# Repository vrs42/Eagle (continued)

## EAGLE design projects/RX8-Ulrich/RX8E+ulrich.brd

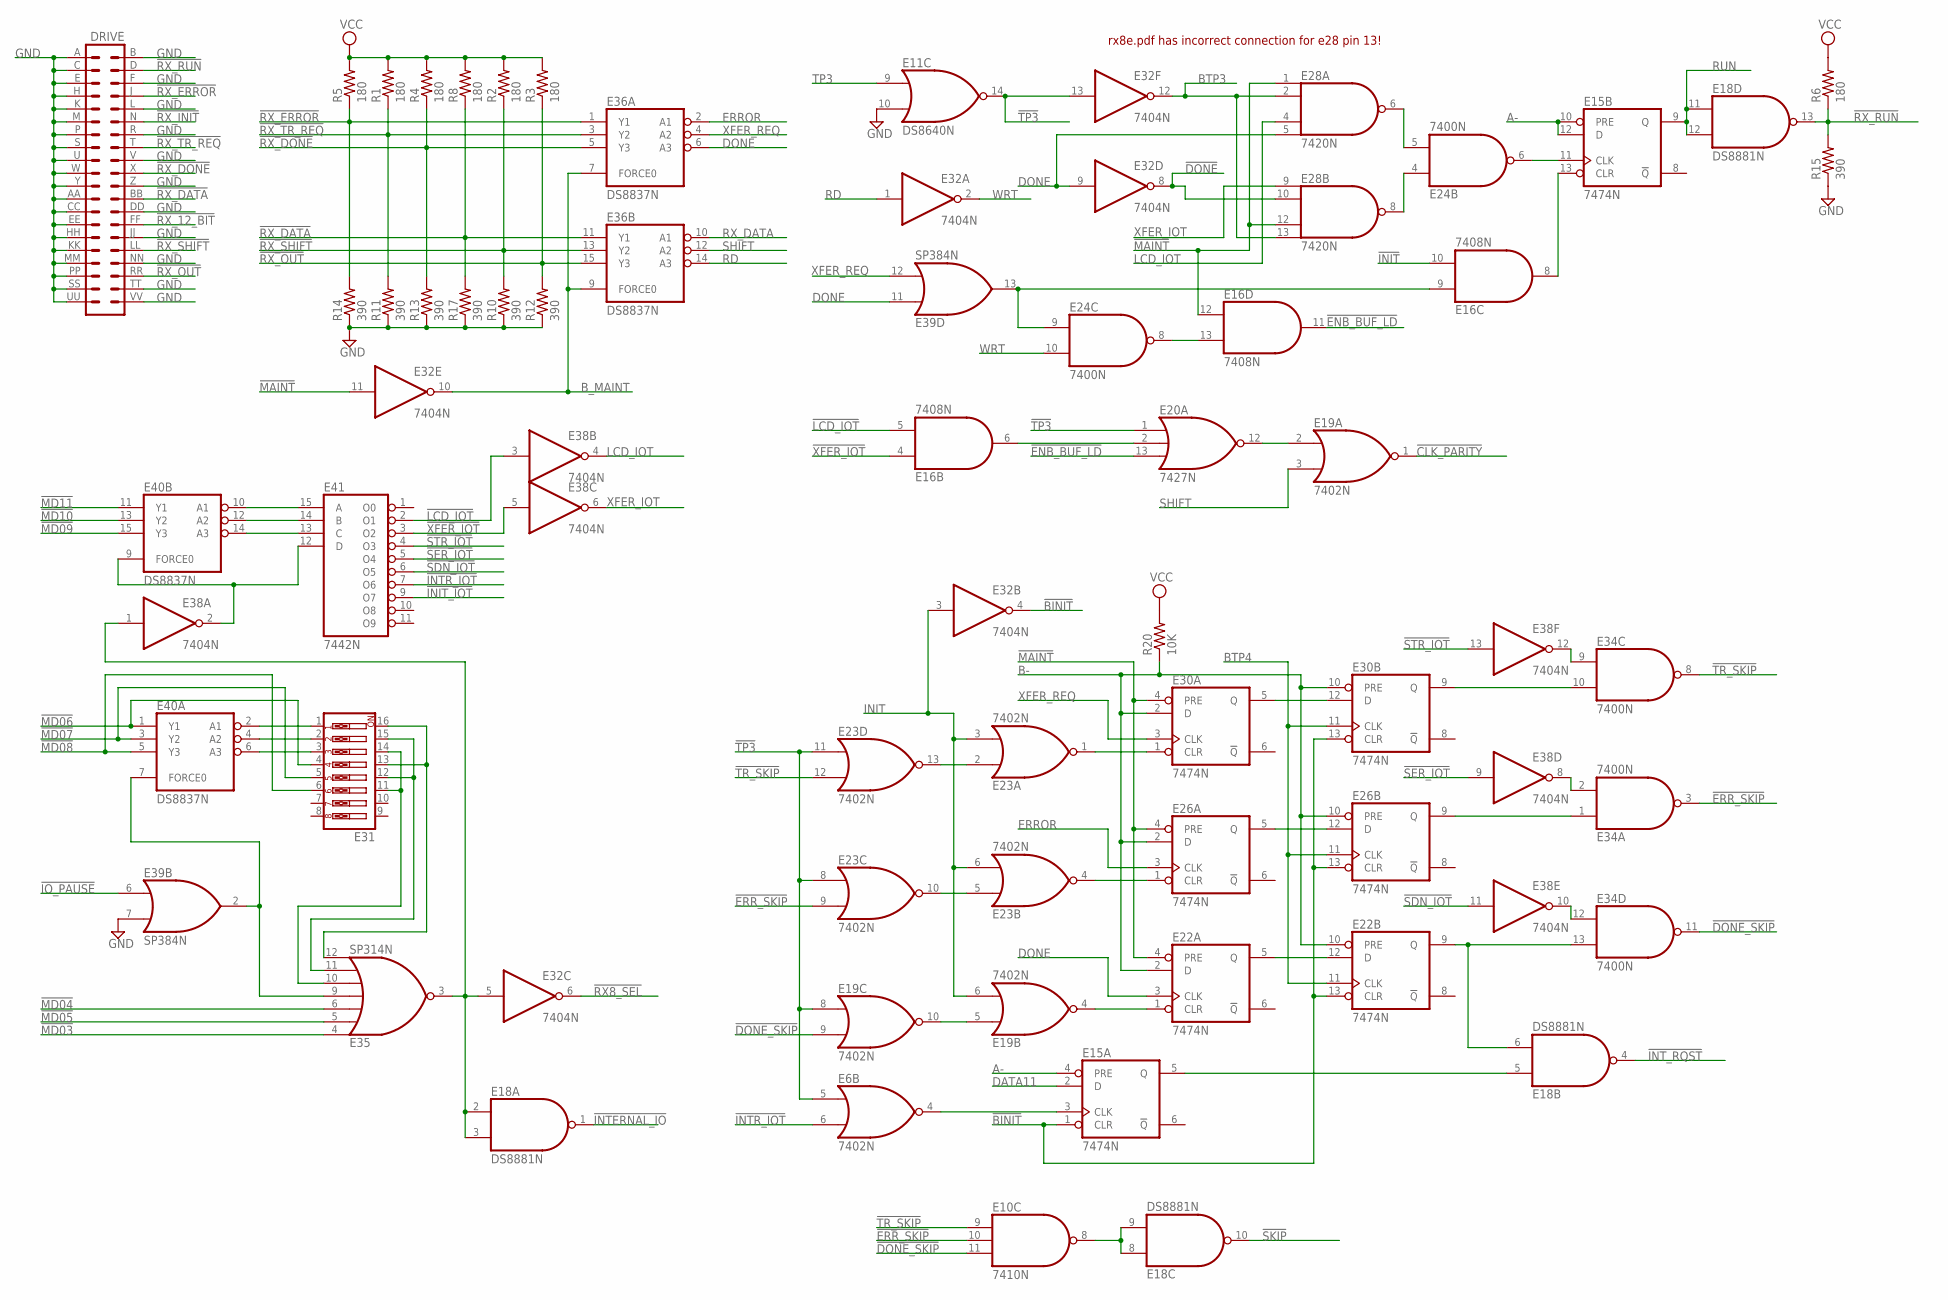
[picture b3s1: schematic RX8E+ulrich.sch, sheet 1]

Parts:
DRIVE: DEC40PINH
E6, E19, E23: 7402N; DIL14
E10: 7410N; DIL14
E11: DS8640N; DIL14
E15, E22, E26, E30: 7474N; DIL14
E16: 7408N; DIL14
E18: DS8881N; DIL14
E20: 7427N; DIL14
E24, E34: 7400N; DIL14
E28: 7420N; DIL14
E31: SW_DIP-8; EDG-08
E32, E38: 7404N; DIL14
E35: SP314N; DIL14
E36, E40: DS8837N; DIL16
E39: SP384N; DIL14
E41: 7442N; DIL16
R1, R2, R3, R4, R5, R6, R8: 180; 0207/10
R10, R11, R12, R13, R14, R15, R17: 390; 0207/10
R20: 10K; 0207/10

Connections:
!BINIT: E15.1 (CLR), E22.13 (CLR), E26.13 (CLR), E30.13 (CLR), E32.4 (O)
!CLK_PARITY: E19.1 (O); also elsewhere on the board
!DONE: E28.10 (I1), E32.8 (O); also elsewhere on the board
!DONE_SKIP: E10.11 (I2), E19.9 (I1), E34.11 (O); also elsewhere on the board
!ENB_BUF_LD: E16.11 (O), E20.13 (I2); also elsewhere on the board
!ERR_SKIP: E10.10 (I1), E23.9 (I1), E34.3 (O)
!INIT: E16.10 (I1); also elsewhere on the board
!INIT_IOT: E41.9 (O7); also elsewhere on the board
!INTERNAL_IO: E18.1 (O); also elsewhere on the board
!INTR_IOT: E6.6 (I1), E41.7 (O6)
!INT_RQST: E18.4 (O); also elsewhere on the board
!IO_PAUSE: E39.6 (I0); also elsewhere on the board
!LCD_IOT: E16.5 (I1), E38.3 (I), E41.2 (O1); also elsewhere on the board
!MAINT: E16.12 (I0), E22.4 (PRE), E26.4 (PRE), E28.1 (I0), E28.12 (I2), E30.4 (PRE), E32.11 (I); also elsewhere on the board
!MD03: E35.4 (I0); also elsewhere on the board
!MD04: E35.6 (I2); also elsewhere on the board
!MD05: E35.5 (I1); also elsewhere on the board
!MD06: E31.4, E40.1 (Y1); also elsewhere on the board
!MD07: E31.5, E40.3 (Y2); also elsewhere on the board
!MD08: E31.6, E40.5 (Y3); also elsewhere on the board
!MD09: E40.15 (Y3); also elsewhere on the board
!MD10: E40.13 (Y2); also elsewhere on the board
!MD11: E40.11 (Y1); also elsewhere on the board
!RX8_SEL: E32.6 (O); also elsewhere on the board
!RX_12_BIT: DRIVE.FF (28); also elsewhere on the board
!RX_DATA: DRIVE.BB (24), E36.11 (Y1), R8.1, R17.2; also elsewhere on the board
!RX_DONE: DRIVE.X (20), E36.5 (Y3), R4.1, R13.2
!RX_ERROR: DRIVE.J (8), E36.1 (Y1), R5.1, R14.2
!RX_INIT: DRIVE.N (12); also elsewhere on the board
!RX_OUT: DRIVE.RR (36), E36.15 (Y3), R3.1, R12.2
!RX_RUN: DRIVE.D (4), E18.13 (O), R6.1, R15.2
!RX_SHIFT: DRIVE.LL (32), E36.13 (Y2), R2.1, R10.2
!RX_TR_REQ: DRIVE.T (16), E36.3 (Y2), R1.1, R11.2
!SDN_IOT: E38.11 (I), E41.6 (O5)
!SER_IOT: E38.9 (I), E41.5 (O4)
!SKIP: E18.10 (O); also elsewhere on the board
!STR_IOT: E38.13 (I), E41.4 (O3)
!TP3: E6.5 (I0), E11.14 (O), E19.8 (I0), E20.1 (I0), E23.8 (I0), E23.11 (I0), E32.13 (I); also elsewhere on the board
!TR_SKIP: E10.9 (I0), E23.12 (I1), E34.8 (O); also elsewhere on the board
!XFER_IOT: E16.4 (I0), E38.5 (I), E41.3 (O2); also elsewhere on the board
A-: E15.4 (PRE), E15.10 (PRE), E15.12 (D); also elsewhere on the board
B-: E22.2 (D), E22.10 (PRE), E26.2 (D), E26.10 (PRE), E30.2 (D), E30.10 (PRE), R20.1; also elsewhere on the board
BTP3: E28.2 (I1), E28.13 (I3), E32.12 (O); also elsewhere on the board
BTP4: E22.11 (CLK), E26.11 (CLK), E30.11 (CLK); also elsewhere on the board
B_MAINT: E32.10 (O), E36.7 (FORCE0), E36.9 (FORCE0)
DATA11: E15.2 (D); also elsewhere on the board
DONE: E22.3 (CLK), E28.5 (I3), E32.9 (I), E36.6 (A3), E39.11 (I0); also elsewhere on the board
ERROR: E26.3 (CLK), E36.2 (A1)
GND: DRIVE.A (1), DRIVE.AA (23), DRIVE.B (2), DRIVE.C (3), DRIVE.CC (25), DRIVE.DD (26), DRIVE.E (5), DRIVE.EE (27), DRIVE.F (6), DRIVE.H (7), DRIVE.HH (29), DRIVE.JJ (30), DRIVE.K (9), DRIVE.KK (31), DRIVE.L (10), DRIVE.M (11), DRIVE.MM (33), DRIVE.NN (34), DRIVE.P (13), DRIVE.PP (35), DRIVE.R (14), DRIVE.S (15), DRIVE.SS (37), DRIVE.TT (38), DRIVE.U (17), DRIVE.UU (39), DRIVE.V (18), DRIVE.VV (40), DRIVE.W (19), DRIVE.Y (21), DRIVE.Z (22), E6.7 (GND), E10.7 (GND), E11.1 (GND), E11.10 (I1), E15.7 (GND), E16.7 (GND), E18.7 (GND), E19.7 (GND), E20.7 (GND), E22.7 (GND), E23.7 (GND), E24.7 (GND), E26.7 (GND), E28.7 (GND), E30.7 (GND), E32.7 (GND), E34.7 (GND), E35.1 (GND), E36.8 (GND), E38.7 (GND), E39.1 (GND), E39.7 (I1), E40.8 (GND), E41.8 (GND), R10.1, R11.1, R12.1, R13.1, R14.1, R15.1, R17.1; also elsewhere on the board
INIT: E19.6 (I1), E23.3 (I1), E23.6 (I1), E32.3 (I); also elsewhere on the board
LCD_IOT: E28.4 (I2), E38.4 (O); also elsewhere on the board
unnamed: E31.11, E31.14, E35.10 (I4)
unnamed: E31.12, E31.15, E35.11 (I5)
unnamed: E31.13, E31.16, E35.12 (I6)
unnamed: E31.3, E40.6 (A3)
unnamed: E31.2, E40.4 (A2)
unnamed: E31.1, E40.2 (A1)
unnamed: E35.9 (I3), E39.2 (O), E40.7 (FORCE0)
unnamed: E18.2 (I0), E18.3 (I1), E32.5 (I), E35.3 (O), E38.1 (I)
unnamed: E19.5 (I0), E19.10 (O)
unnamed: E38.2 (O), E40.9 (FORCE0), E41.12 (D)
unnamed: E40.14 (A3), E41.13 (C)
unnamed: E40.12 (A2), E41.14 (B)
unnamed: E40.10 (A1), E41.15 (A)
unnamed: E19.4 (O), E22.1 (CLR)
unnamed: E23.4 (O), E26.1 (CLR)
unnamed: E23.5 (I0), E23.10 (O)
unnamed: E23.2 (I0), E23.13 (O)
unnamed: E23.1 (O), E30.1 (CLR)
unnamed: E30.5 (Q), E30.12 (D)
unnamed: E26.5 (Q), E26.12 (D)
unnamed: E22.5 (Q), E22.12 (D)
unnamed: E18.6 (I1), E22.9 (Q), E34.13 (I1)
unnamed: E26.9 (Q), E34.1 (I0)
unnamed: E6.4 (O), E15.3 (CLK)
unnamed: E30.9 (Q), E34.10 (I1)
unnamed: E34.2 (I1), E38.8 (O)
unnamed: E34.12 (I0), E38.10 (O)
unnamed: E34.9 (I0), E38.12 (O)
unnamed: E15.5 (Q), E18.5 (I0)
unnamed: E10.8 (O), E18.8 (I0), E18.9 (I1)
unnamed: E24.5 (I1), E28.6 (O)
unnamed: E16.6 (O), E20.2 (I1)
unnamed: E24.4 (I0), E28.8 (O)
unnamed: E16.9 (I0), E24.9 (I0), E39.13 (O)
unnamed: E16.13 (I1), E24.8 (O)
unnamed: E15.13 (CLR), E16.8 (O)
unnamed: E19.2 (I0), E20.12 (O)
unnamed: E15.11 (CLK), E24.6 (O)
RD: E32.1 (I), E36.14 (A3); also elsewhere on the board
RUN: E15.9 (Q), E18.11 (I0), E18.12 (I1); also elsewhere on the board
RX_DATA: E36.10 (A1); also elsewhere on the board
SHIFT: E19.3 (I1), E36.12 (A2)
TP3: E11.9 (I0); also elsewhere on the board
VCC: E6.14 (VCC), E10.14 (VCC), E11.8 (VCC), E15.14 (VCC), E16.14 (VCC), E18.14 (VCC), E19.14 (VCC), E20.14 (VCC), E22.14 (VCC), E23.14 (VCC), E24.14 (VCC), E26.14 (VCC), E28.14 (VCC), E30.14 (VCC), E32.14 (VCC), E34.14 (VCC), E35.8 (VCC), E36.16 (VCC), E38.14 (VCC), E39.8 (VCC), E40.16 (VCC), E41.16 (VCC), R1.2, R2.2, R3.2, R4.2, R5.2, R6.2, R8.2, R20.2; also elsewhere on the board
WRT: E24.10 (I1), E32.2 (O); also elsewhere on the board
XFER_IOT: E28.9 (I0), E38.6 (O); also elsewhere on the board
XFER_REQ: E30.3 (CLK), E36.4 (A2), E39.12 (I1)

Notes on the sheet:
rx8e.pdf has incorrect connection for e28 pin 13!

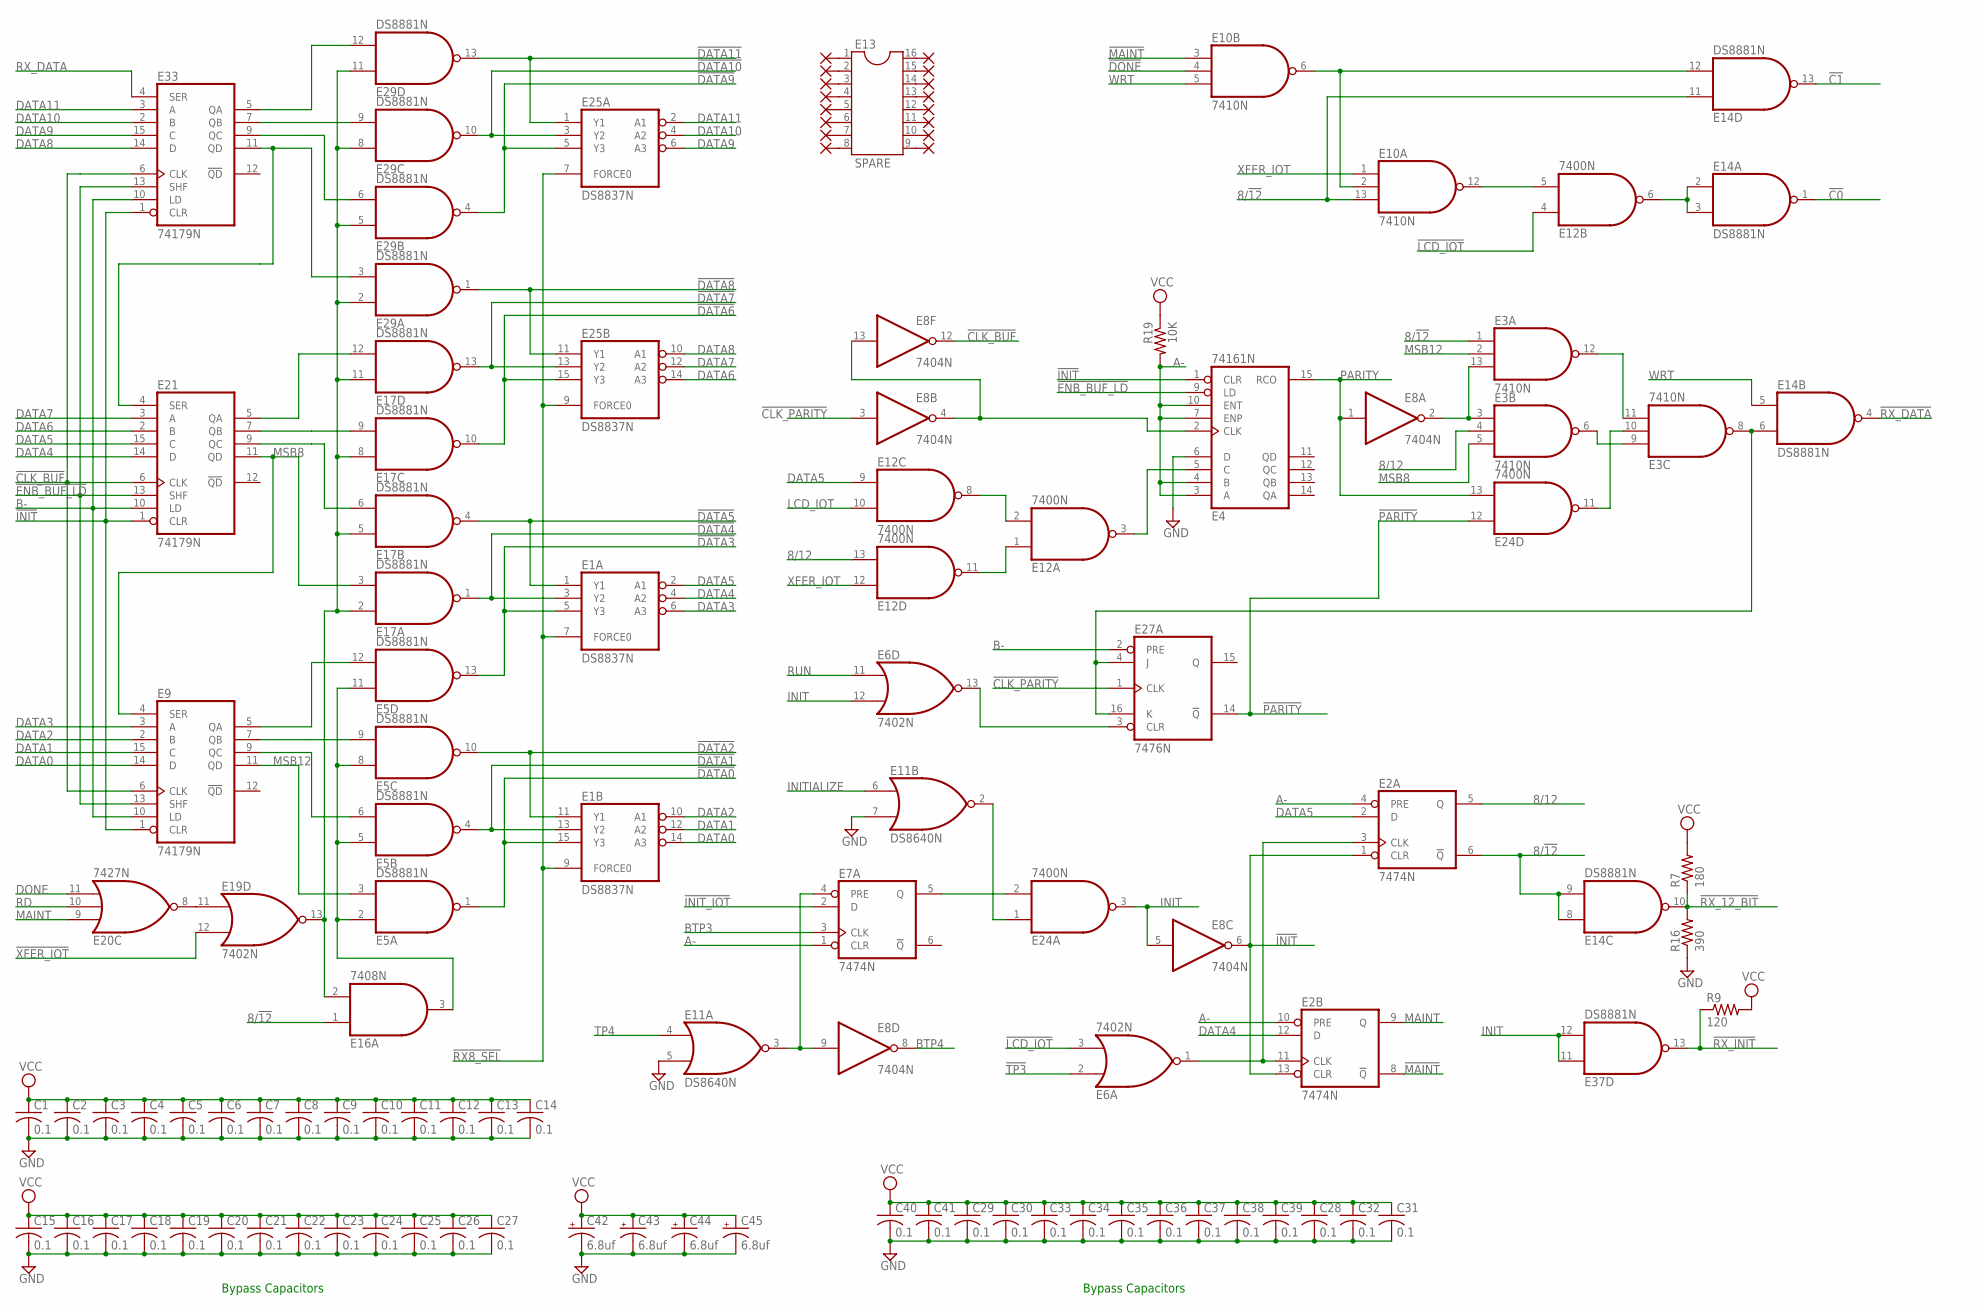
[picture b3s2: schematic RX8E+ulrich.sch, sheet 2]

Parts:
C1, C2, C3, C4, C5, C6, C7, C8, C9, C10, C11, C12, C13, C14, C15, C16, C17, C18, C19, C20, C21, C22, C23, C24, C25, C26, C27, C28, C29, C30, C31, C32, C33, C34, C35, C36, C37, C38, C39, C40, C41: 0.1; C050-025X075
C42, C43, C44, C45: 6.8uf; E22-6
E1, E25: DS8837N; DIL16
E2, E7: 7474N; DIL14
E3, E10: 7410N; DIL14
E4: 74161N; DIL16
E5, E14, E17, E29, E37: DS8881N; DIL14
E6, E19: 7402N; DIL14
E8: 7404N; DIL14
E9, E21, E33: 74179N; DIL16
E11: DS8640N; DIL14
E12, E24: 7400N; DIL14
E13: SPARE; DIL16
E16: 7408N; DIL14
E20: 7427N; DIL14
E27: 7476N; DIL16
PAD10, PAD11, PAD12, PAD13, PAD14, PAD15, PAD16, PAD17, PAD20, PAD21, PAD22, PAD23, PAD24, PAD25, PAD26, PAD27: 1,6/0,8
R7: 180; 0207/10
R9: 120; 0207/10
R16: 390; 0207/10
R19: 10K; 0207/10

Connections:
8/12: E2.5 (Q), E3.4 (I1), E12.13 (I1)
8/!12: E2.6 (!Q), E3.1 (I0), E10.13 (I2), E14.8 (I0), E14.9 (I1), E14.11 (I0), E16.1 (I0)
!C0: E14.1 (O); also elsewhere on the board
!C1: E14.13 (O); also elsewhere on the board
!CLK_BUF: E8.12 (O), E9.6 (CLK), E21.6 (CLK), E33.6 (CLK)
!CLK_PARITY: E8.3 (I), E27.1 (CLK); also elsewhere on the board
!DATA0: E1.15 (Y3), E5.1 (O); also elsewhere on the board
!DATA1: E1.13 (Y2), E5.4 (O); also elsewhere on the board
!DATA2: E1.11 (Y1), E5.10 (O); also elsewhere on the board
!DATA3: E1.5 (Y3), E5.13 (O); also elsewhere on the board
!DATA4: E1.3 (Y2), E17.1 (O); also elsewhere on the board
!DATA5: E1.1 (Y1), E17.4 (O); also elsewhere on the board
!DATA6: E17.10 (O), E25.15 (Y3); also elsewhere on the board
!DATA7: E17.13 (O), E25.13 (Y2); also elsewhere on the board
!DATA8: E25.11 (Y1), E29.1 (O); also elsewhere on the board
!DATA9: E25.5 (Y3), E29.4 (O); also elsewhere on the board
!DATA10: E25.3 (Y2), E29.10 (O); also elsewhere on the board
!DATA11: E25.1 (Y1), E29.13 (O); also elsewhere on the board
!DONE: E10.4 (I1); also elsewhere on the board
!ENB_BUF_LD: E4.9 (LD), E9.13 (SHF), E21.13 (SHF), E33.13 (SHF); also elsewhere on the board
!INIT: E2.1 (CLR), E2.13 (CLR), E4.1 (CLR), E8.6 (O), E9.1 (CLR), E21.1 (CLR), E33.1 (CLR); also elsewhere on the board
!INIT_IOT: E7.2 (D); also elsewhere on the board
!LCD_IOT: E6.3 (I1), E12.4 (I0); also elsewhere on the board
!MAINT: E2.8 (!Q), E10.3 (I0); also elsewhere on the board
!PARITY: E24.12 (I0), E27.14 (!Q)
!RX8_SEL: E1.7 (FORCE0), E1.9 (FORCE0), E25.7 (FORCE0), E25.9 (FORCE0); also elsewhere on the board
!RX_12_BIT: E14.10 (O), R7.1, R16.2; also elsewhere on the board
!RX_DATA: E14.4 (O); also elsewhere on the board
!RX_INIT: E37.13 (O), R9.1; also elsewhere on the board
!TP3: E6.2 (I0); also elsewhere on the board
!XFER_IOT: E19.12 (I1); also elsewhere on the board
A-: E2.4 (PRE), E2.10 (PRE), E4.3 (A), E4.4 (B), E4.7 (ENP), E4.10 (ENT), E7.1 (CLR), R19.2; also elsewhere on the board
B-: E9.10 (LD), E21.10 (LD), E27.2 (PRE), E33.10 (LD); also elsewhere on the board
BTP3: E7.3 (CLK); also elsewhere on the board
BTP4: E8.8 (O); also elsewhere on the board
DATA0: E1.14 (A3), E9.14 (D)
DATA1: E1.12 (A2), E9.15 (C)
DATA2: E1.10 (A1), E9.2 (B)
DATA3: E1.6 (A3), E9.3 (A)
DATA4: E1.4 (A2), E2.12 (D), E21.14 (D)
DATA5: E1.2 (A1), E2.2 (D), E12.9 (I0), E21.15 (C)
DATA6: E21.2 (B), E25.14 (A3)
DATA7: E21.3 (A), E25.12 (A2)
DATA8: E25.10 (A1), E33.14 (D)
DATA9: E25.6 (A3), E33.15 (C)
DATA10: E25.4 (A2), E33.2 (B)
DATA11: E25.2 (A1), E33.3 (A); also elsewhere on the board
DONE: E20.11 (I2); also elsewhere on the board
GND: C1.2, C2.2, C3.2, C4.2, C5.2, C6.2, C7.2, C8.2, C9.2, C10.2, C11.2, C12.2, C13.2, C14.2, C15.2, C16.2, C17.2, C18.2, C19.2, C20.2, C21.2, C22.2, C23.2, C24.2, C25.2, C26.2, C27.2, C28.2, C29.2, C30.2, C31.2, C32.2, C33.2, C34.2, C35.2, C36.2, C37.2, C38.2, C39.2, C40.2, C41.2, C42.-, C43.-, C44.-, C45.-, E1.8 (GND), E2.7 (GND), E3.7 (GND), E4.6 (D), E4.8 (GND), E5.7 (GND), E6.7 (GND), E7.7 (GND), E8.7 (GND), E9.8 (GND), E10.7 (GND), E11.1 (GND), E11.5 (I1), E11.7 (I1), E12.7 (GND), E14.7 (GND), E16.7 (GND), E17.7 (GND), E19.7 (GND), E20.7 (GND), E21.8 (GND), E24.7 (GND), E25.8 (GND), E27.13 (GND), E29.7 (GND), E33.8 (GND), E37.7 (GND), R16.1; also elsewhere on the board
INIT: E6.12 (I1), E8.5 (I), E24.3 (O), E37.11 (I0), E37.12 (I1); also elsewhere on the board
INITIALIZE: E11.6 (I0); also elsewhere on the board
LCD_IOT: E12.10 (I1); also elsewhere on the board
MAINT: E2.9 (Q), E20.9 (I0)
MSB8: E3.5 (I2), E9.4 (SER), E17.3 (I1), E21.11 (QD)
MSB12: E3.2 (I1), E5.3 (I1), E9.11 (QD)
unnamed: E5.9 (I1), E9.7 (QB)
unnamed: E16.2 (I1), E17.2 (I0), E17.5 (I0), E17.8 (I0), E17.11 (I0), E19.13 (O), E29.2 (I0), E29.5 (I0), E29.8 (I0), E29.11 (I0)
unnamed: E19.11 (I0), E20.8 (O)
unnamed: E5.2 (I0), E5.5 (I0), E5.8 (I0), E5.11 (I0), E16.3 (O)
unnamed: E13.1, PAD10.1
unnamed: E13.2, PAD11.1
unnamed: E13.3, PAD12.1
unnamed: E13.4, PAD13.1
unnamed: E13.5, PAD14.1
unnamed: E13.6, PAD15.1
unnamed: E13.7, PAD16.1
unnamed: E13.8, PAD17.1
unnamed: E4.5 (C), E12.3 (O)
unnamed: E12.6 (O), E14.2 (I0), E14.3 (I1)
unnamed: E13.16, PAD20.1
unnamed: E13.15, PAD21.1
unnamed: E13.14, PAD22.1
unnamed: E13.13, PAD23.1
unnamed: E13.12, PAD24.1
unnamed: E13.11, PAD25.1
unnamed: E13.10, PAD26.1
unnamed: E13.9, PAD27.1
unnamed: E21.4 (SER), E29.3 (I1), E33.11 (QD)
unnamed: E10.12 (O), E12.5 (I1)
unnamed: E5.6 (I1), E9.9 (QC)
unnamed: E10.2 (I1), E10.6 (O), E14.12 (I1)
unnamed: E12.1 (I0), E12.11 (O)
unnamed: E12.2 (I1), E12.8 (O)
unnamed: E3.3 (I0), E3.13 (I2), E8.2 (O)
unnamed: E3.11 (I2), E3.12 (O)
unnamed: E3.6 (O), E3.9 (I0)
unnamed: E3.10 (I1), E24.11 (O)
unnamed: E3.8 (O), E14.6 (I1), E27.4 (J), E27.16 (K)
unnamed: E7.4 (PRE), E8.9 (I), E11.3 (O)
unnamed: E4.2 (CLK), E8.4 (O), E8.13 (I)
unnamed: E7.5 (Q), E24.2 (I1)
unnamed: E6.13 (O), E27.3 (CLR)
unnamed: E11.2 (O), E24.1 (I0)
unnamed: E2.3 (CLK), E2.11 (CLK), E6.1 (O)
unnamed: E5.12 (I1), E9.5 (QA)
unnamed: E17.6 (I1), E21.9 (QC)
unnamed: E17.9 (I1), E21.7 (QB)
unnamed: E17.12 (I1), E21.5 (QA)
unnamed: E29.12 (I1), E33.5 (QA)
unnamed: E29.6 (I1), E33.9 (QC)
unnamed: E29.9 (I1), E33.7 (QB)
PARITY: E4.15 (RCO), E8.1 (I), E24.13 (I1); also elsewhere on the board
RD: E20.10 (I1); also elsewhere on the board
RUN: E6.11 (I0); also elsewhere on the board
RX_DATA: E33.4 (SER); also elsewhere on the board
TP4: E11.4 (I0); also elsewhere on the board
VCC: C1.1, C2.1, C3.1, C4.1, C5.1, C6.1, C7.1, C8.1, C9.1, C10.1, C11.1, C12.1, C13.1, C14.1, C15.1, C16.1, C17.1, C18.1, C19.1, C20.1, C21.1, C22.1, C23.1, C24.1, C25.1, C26.1, C27.1, C28.1, C29.1, C30.1, C31.1, C32.1, C33.1, C34.1, C35.1, C36.1, C37.1, C38.1, C39.1, C40.1, C41.1, C42.+, C43.+, C44.+, C45.+, E1.16 (VCC), E2.14 (VCC), E3.14 (VCC), E4.16 (VCC), E5.14 (VCC), E6.14 (VCC), E7.14 (VCC), E8.14 (VCC), E9.16 (VCC), E10.14 (VCC), E11.8 (VCC), E12.14 (VCC), E14.14 (VCC), E16.14 (VCC), E17.14 (VCC), E19.14 (VCC), E20.14 (VCC), E21.16 (VCC), E24.14 (VCC), E25.16 (VCC), E27.5 (VCC), E29.14 (VCC), E33.16 (VCC), E37.14 (VCC), R7.2, R9.2, R19.1; also elsewhere on the board
WRT: E10.5 (I2), E14.5 (I0); also elsewhere on the board
XFER_IOT: E10.1 (I0), E12.12 (I0); also elsewhere on the board

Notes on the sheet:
Bypass Capacitors

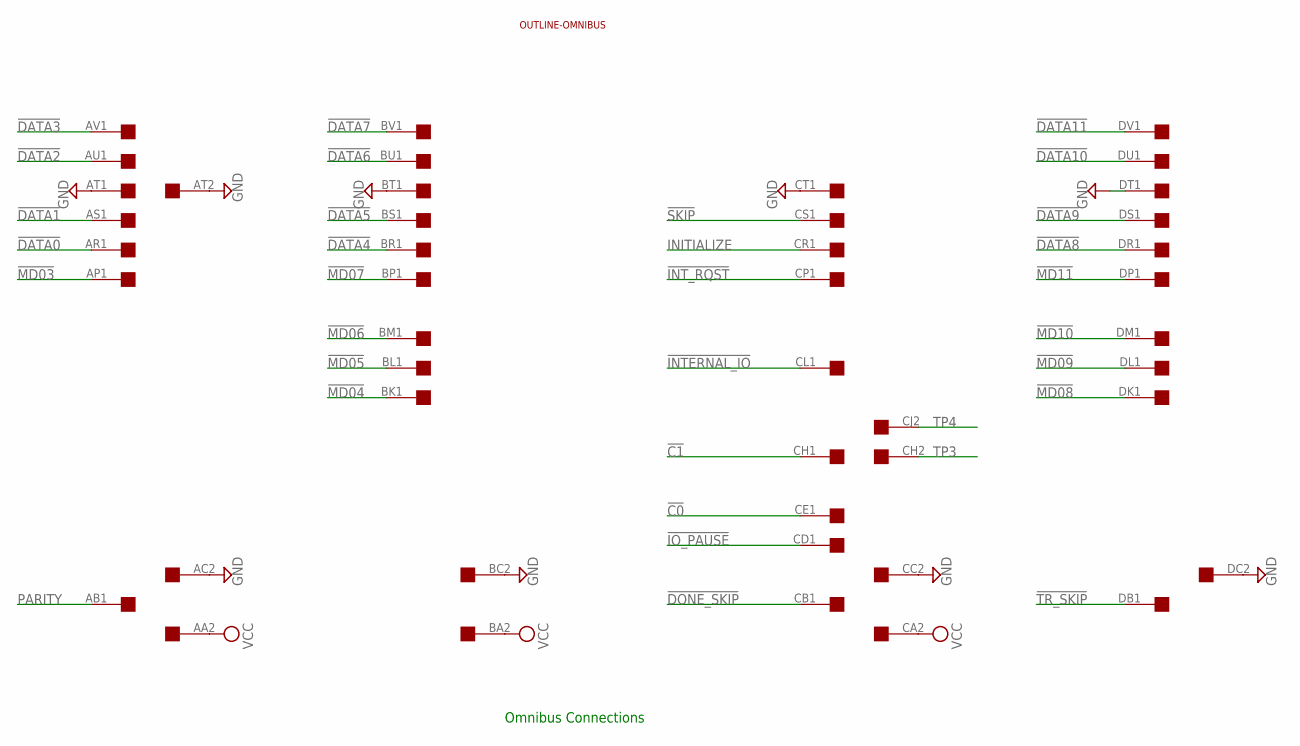
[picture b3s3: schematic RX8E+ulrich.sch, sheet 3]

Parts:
U$2: QUAD; EDGE-CON8
U$5: OUTLINE-OMNIBUS; OMNIBUS

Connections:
!C0: U$2.CE1; also elsewhere on the board
!C1: U$2.CH1; also elsewhere on the board
!DATA0: U$2.AR1; also elsewhere on the board
!DATA1: U$2.AS1; also elsewhere on the board
!DATA2: U$2.AU1; also elsewhere on the board
!DATA3: U$2.AV1; also elsewhere on the board
!DATA4: U$2.BR1; also elsewhere on the board
!DATA5: U$2.BS1; also elsewhere on the board
!DATA6: U$2.BU1; also elsewhere on the board
!DATA7: U$2.BV1; also elsewhere on the board
!DATA8: U$2.DR1; also elsewhere on the board
!DATA9: U$2.DS1; also elsewhere on the board
!DATA10: U$2.DU1; also elsewhere on the board
!DATA11: U$2.DV1; also elsewhere on the board
!DONE_SKIP: U$2.CB1; also elsewhere on the board
!INTERNAL_IO: U$2.CL1; also elsewhere on the board
!INT_RQST: U$2.CP1; also elsewhere on the board
!IO_PAUSE: U$2.CD1; also elsewhere on the board
!MD03: U$2.AP1; also elsewhere on the board
!MD04: U$2.BK1; also elsewhere on the board
!MD05: U$2.BL1; also elsewhere on the board
!MD06: U$2.BM1; also elsewhere on the board
!MD07: U$2.BP1; also elsewhere on the board
!MD08: U$2.DK1; also elsewhere on the board
!MD09: U$2.DL1; also elsewhere on the board
!MD10: U$2.DM1; also elsewhere on the board
!MD11: U$2.DP1; also elsewhere on the board
!SKIP: U$2.CS1; also elsewhere on the board
!TR_SKIP: U$2.DB1; also elsewhere on the board
GND: U$2.AC2, U$2.AT1, U$2.AT2, U$2.BC2, U$2.BT1, U$2.CC2, U$2.CT1, U$2.DC2, U$2.DT1; also elsewhere on the board
INITIALIZE: U$2.CR1; also elsewhere on the board
PARITY: U$2.AB1; also elsewhere on the board
TP3: U$2.CH2; also elsewhere on the board
TP4: U$2.CJ2; also elsewhere on the board
VCC: U$2.AA2, U$2.BA2, U$2.CA2; also elsewhere on the board

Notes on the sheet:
Omnibus Connections

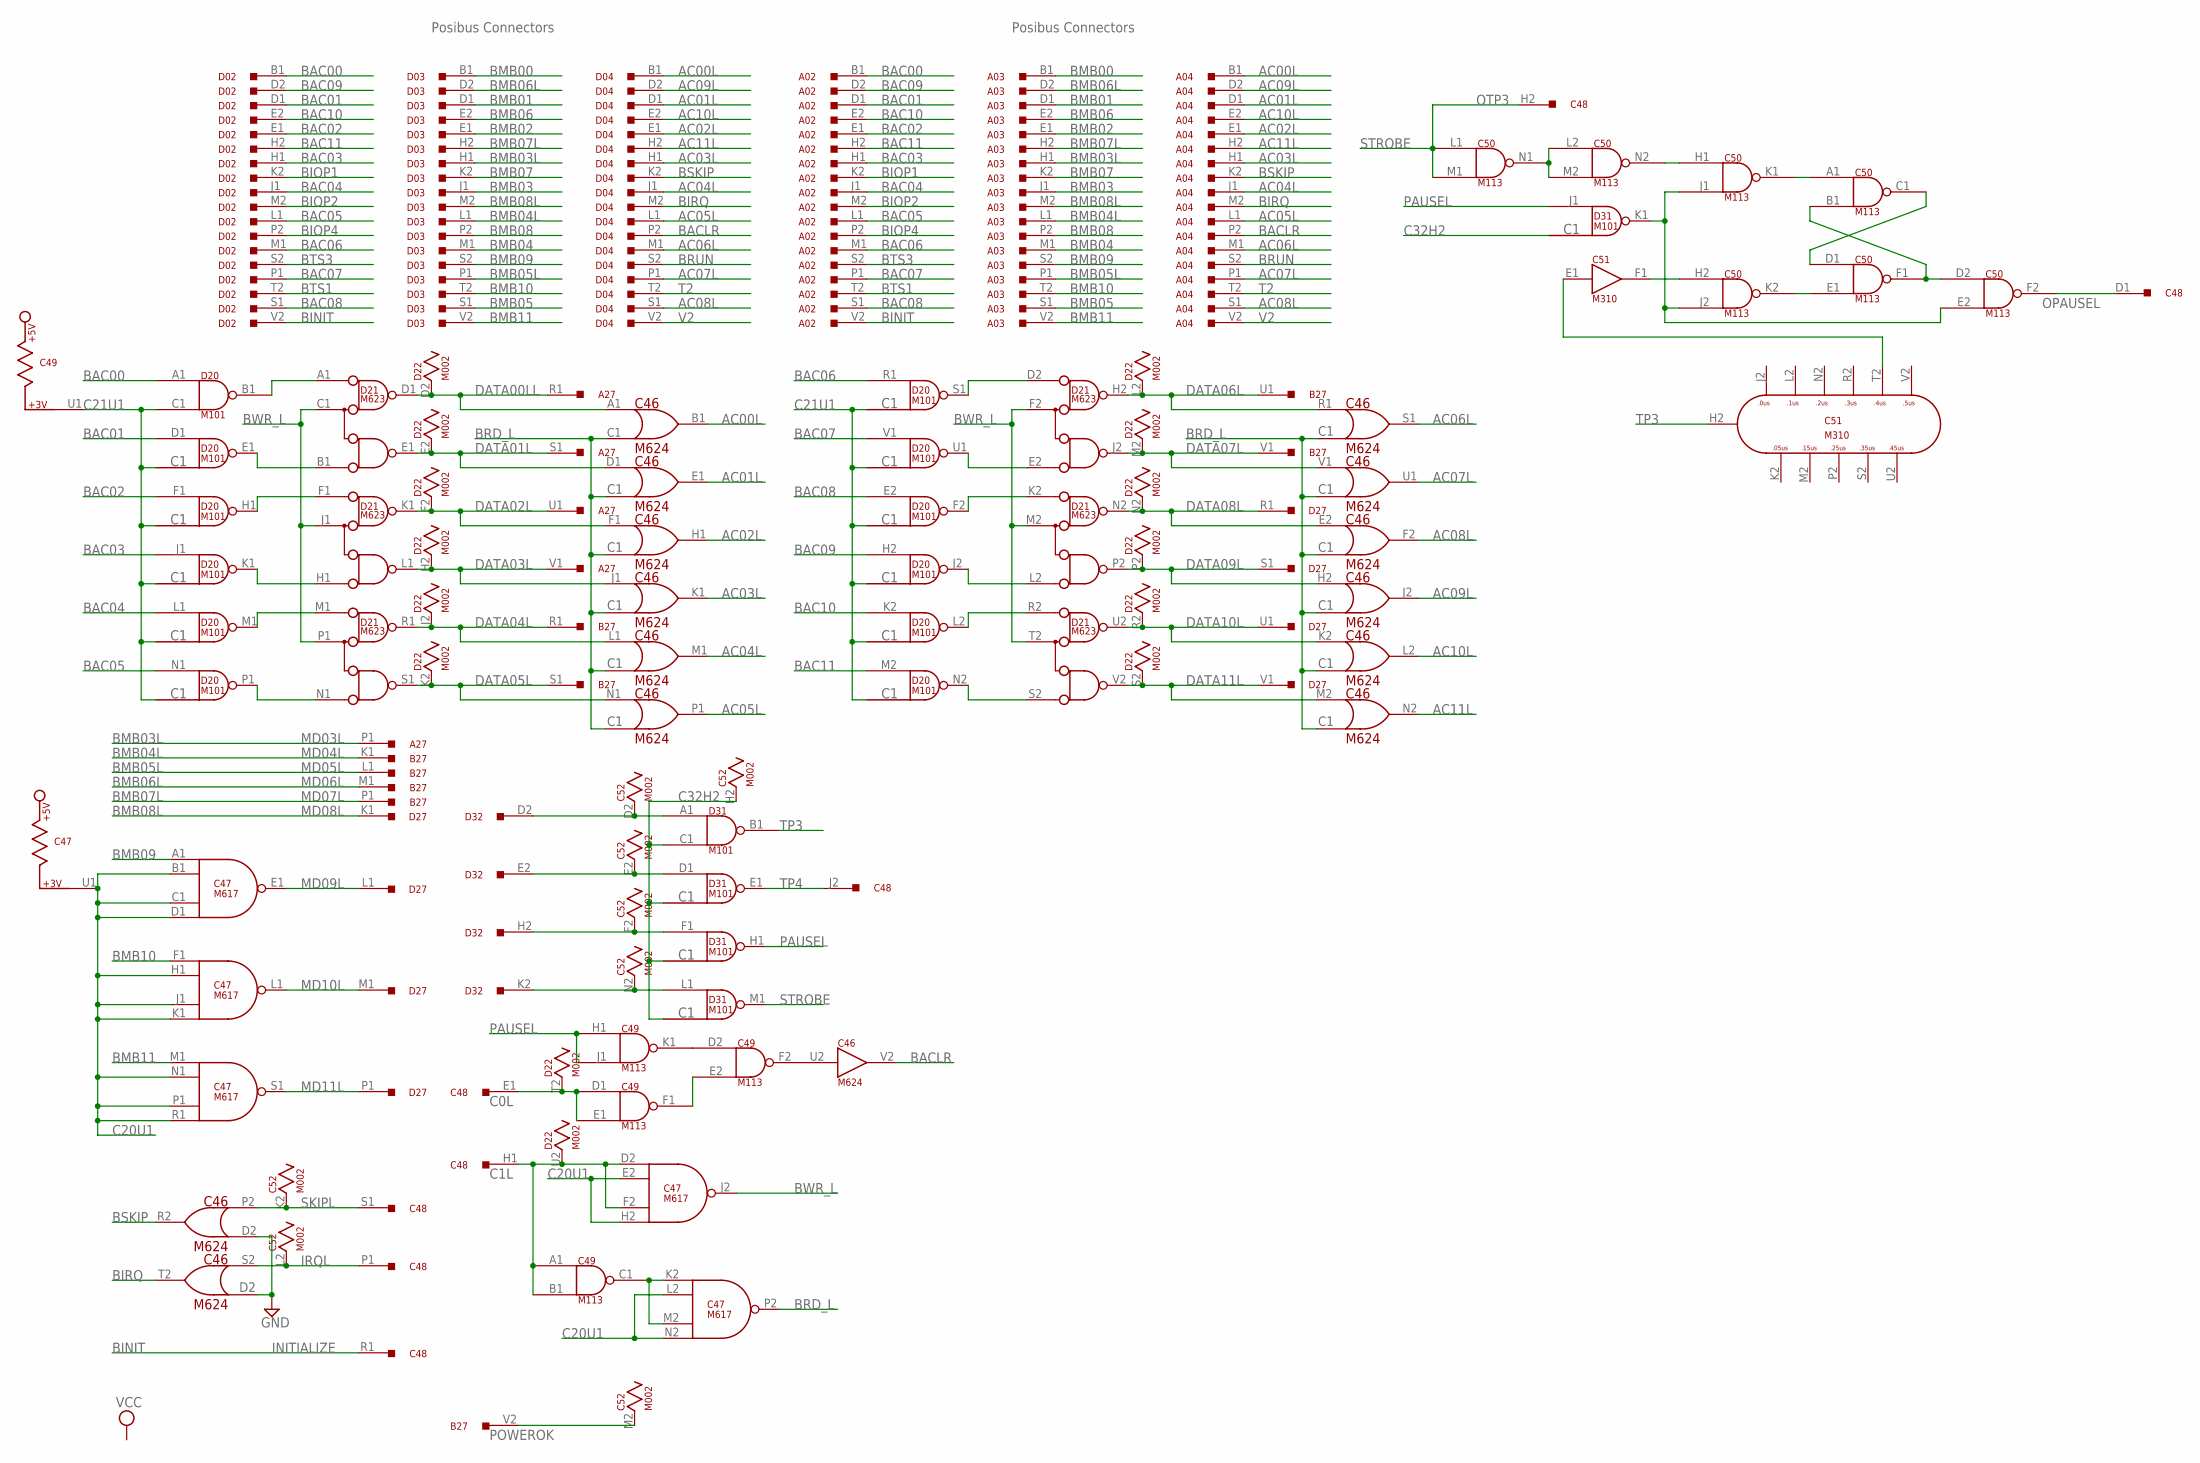
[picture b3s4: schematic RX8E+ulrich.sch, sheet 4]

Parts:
A02, A03, A04: M903; H807
A27: M916; H807
B27: M916; H807
C46: M624; H807
C47: M617; H807
C48: M916; H807
C49, C50: M113; H807
C51: M310; H807
C52: M002; H807
D02, D03, D04, D32: M903; H807
D20, D31: M101; H807
D21: M623; H807
D22: M002; H807
D27: M916; H807

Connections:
AC00L: A04.B1, C46.B1 (OUT), D04.B1
AC01L: A04.D1, C46.E1 (OUT), D04.D1
AC02L: A04.E1, C46.H1 (OUT), D04.E1
AC03L: A04.H1, C46.K1 (OUT), D04.H1
AC04L: A04.J1, C46.M1 (OUT), D04.J1
AC05L: A04.L1, C46.P1 (OUT), D04.L1
AC06L: A04.M1, C46.S1 (OUT), D04.M1
AC07L: A04.P1, C46.U1 (OUT), D04.P1
AC08L: A04.S1, C46.F2 (OUT), D04.S1
AC09L: A04.D2, C46.J2 (OUT), D04.D2
AC10L: A04.E2, C46.L2 (OUT), D04.E2
AC11L: A04.H2, C46.N2 (OUT), D04.H2
BAC00: A02.B1, D02.B1, D20.A1 (IN1)
BAC01: A02.D1, D02.D1, D20.D1 (IN)
BAC02: A02.E1, D02.E1, D20.F1 (IN)
BAC03: A02.H1, D02.H1, D20.J1 (IN)
BAC04: A02.J1, D02.J1, D20.L1 (IN)
BAC05: A02.L1, D02.L1, D20.N1 (IN)
BAC06: A02.M1, D02.M1, D20.R1 (IN)
BAC07: A02.P1, D02.P1, D20.V1 (IN)
BAC08: A02.S1, D02.S1, D20.E2 (IN)
BAC09: A02.D2, D02.D2, D20.H2 (IN)
BAC10: A02.E2, D02.E2, D20.K2 (IN)
BAC11: A02.H2, D02.H2, D20.M2 (IN)
BACLR: A04.P2, C46.V2 (OUT), D04.P2
BINIT: A02.V2, C48.R1, D02.V2
BIOP1: A02.K2, D02.K2
BIOP2: A02.M2, D02.M2
BIOP4: A02.P2, D02.P2
BIRQ: A04.M2, C46.T2 (OUT), D04.M2
BMB00: A03.B1, D03.B1
BMB01: A03.D1, D03.D1
BMB02: A03.E1, D03.E1
BMB03: A03.J1, D03.J1
BMB03L: A03.H1, A27.P1, D03.H1
BMB04: A03.M1, D03.M1
BMB04L: A03.L1, B27.K1, D03.L1
BMB05: A03.S1, D03.S1
BMB05L: A03.P1, B27.L1, D03.P1
BMB06: A03.E2, D03.E2
BMB06L: A03.D2, B27.M1, D03.D2
BMB07: A03.K2, D03.K2
BMB07L: A03.H2, B27.P1, D03.H2
BMB08: A03.P2, D03.P2
BMB08L: A03.M2, D03.M2, D27.K1
BMB09: A03.S2, C47.A1 (IN1), D03.S2
BMB10: A03.T2, C47.F1 (IN1), D03.T2
BMB11: A03.V2, C47.M1 (IN1), D03.V2
BRD_L: C46.C1 (IN2), C47.P2 (OUT)
BRUN: A04.S2, D04.S2
BSKIP: A04.K2, C46.R2 (OUT), D04.K2
BTS1: A02.T2, D02.T2
BTS3: A02.S2, D02.S2
BWR_L: C47.J2 (OUT), D21.C1 (C), D21.F2 (C), D21.J1 (C), D21.M2 (C), D21.P1 (C), D21.T2 (C)
C0L: C48.E1, C49.D1 (IN1), C49.E1 (IN2), D22.T2
C1L: C47.D2 (IN1), C47.F2 (IN3), C48.H1, C49.A1 (IN1), C49.B1 (IN2), D22.U2
C20U1: C47.B1 (IN2), C47.C1 (IN3), C47.D1 (IN4), C47.E2 (IN2), C47.H1 (IN2), C47.H2 (IN4), C47.J1 (IN3), C47.K1 (IN4), C47.L2 (IN2), C47.N1 (IN2), C47.N2 (IN4), C47.P1 (IN3), C47.R1 (IN4), C47.U1
C21U1: C49.U1, D20.C1 (IN2)
C32H2: C52.H2, D31.C1 (IN2)
DATA00LL: A27.R1, C46.A1 (IN1), D21.D1 (D), D22.D2
DATA01L: A27.S1, C46.D1 (IN), D21.E1 (E), D22.E2
DATA02L: A27.U1, C46.F1 (IN), D21.K1 (D), D22.F2
DATA03L: A27.V1, C46.J1 (IN), D21.L1 (E), D22.H2
DATA04L: B27.R1, C46.L1 (IN), D21.R1 (D), D22.J2
DATA05L: B27.S1, C46.N1 (IN), D21.S1 (E), D22.K2
DATA06L: B27.U1, C46.R1 (IN), D21.H2 (D), D22.L2
DATA07L: B27.V1, C46.V1 (IN), D21.J2 (E), D22.M2
DATA08L: C46.E2 (IN), D21.N2 (D), D22.N2, D27.R1
DATA09L: C46.H2 (IN), D21.P2 (E), D22.P2, D27.S1
DATA10L: C46.K2 (IN), D21.U2 (D), D22.R2, D27.U1
DATA11L: C46.M2 (IN), D21.V2 (E), D22.S2, D27.V1
GND: A02.A1 (GND), A02.C1 (GND), A02.C2 (GND), A02.F1 (GND), A02.F2 (GND), A02.J2 (GND), A02.K1 (GND), A02.L2 (GND), A02.N1 (GND), A02.N2 (GND), A02.R1 (GND), A02.R2 (GND), A02.T1 (GND), A02.U2 (GND), A03.A1 (GND), A03.C1 (GND), A03.C2 (GND), A03.F1 (GND), A03.F2 (GND), A03.J2 (GND), A03.K1 (GND), A03.L2 (GND), A03.N1 (GND), A03.N2 (GND), A03.R1 (GND), A03.R2 (GND), A03.T1 (GND), A03.U2 (GND), A04.A1 (GND), A04.C1 (GND), A04.C2 (GND), A04.F1 (GND), A04.F2 (GND), A04.J2 (GND), A04.K1 (GND), A04.L2 (GND), A04.N1 (GND), A04.N2 (GND), A04.R1 (GND), A04.R2 (GND), A04.T1 (GND), A04.U2 (GND), C46.C2 (GND), C46.D2 (IN2), C46.T1 (GND), C47.C2 (GND), C47.T1 (GND), C49.C2 (GND), C49.T1 (GND), C50.C2 (GND), C50.T1 (GND), C51.C2 (GND), C51.T1 (GND), C52.C2 (GND), D02.A1 (GND), D02.C1 (GND), D02.C2 (GND), D02.F1 (GND), D02.F2 (GND), D02.J2 (GND), D02.K1 (GND), D02.L2 (GND), D02.N1 (GND), D02.N2 (GND), D02.R1 (GND), D02.R2 (GND), D02.T1 (GND), D02.U2 (GND), D03.A1 (GND), D03.C1 (GND), D03.C2 (GND), D03.F1 (GND), D03.F2 (GND), D03.J2 (GND), D03.K1 (GND), D03.L2 (GND), D03.N1 (GND), D03.N2 (GND), D03.R1 (GND), D03.R2 (GND), D03.T1 (GND), D03.U2 (GND), D04.A1 (GND), D04.C1 (GND), D04.C2 (GND), D04.F1 (GND), D04.F2 (GND), D04.J2 (GND), D04.K1 (GND), D04.L2 (GND), D04.N1 (GND), D04.N2 (GND), D04.R1 (GND), D04.R2 (GND), D04.T1 (GND), D04.U2 (GND), D20.C2 (GND), D20.T1 (GND), D21.C2 (GND), D21.T1 (GND), D21.U1 (GND), D21.V1 (GND), D22.C2 (GND), D31.C2 (GND), D31.T1 (GND), D32.A1 (GND), D32.C1 (GND), D32.C2 (GND), D32.F1 (GND), D32.F2 (GND), D32.J2 (GND), D32.K1 (GND), D32.L2 (GND), D32.N1 (GND), D32.N2 (GND), D32.R1 (GND), D32.R2 (GND), D32.T1 (GND), D32.U2 (GND); also elsewhere on the board
IRQL: C46.S2 (IN), C48.P1, C52.L2
MD09L: C47.E1 (OUT), D27.L1
MD10L: C47.L1 (OUT), D27.M1
MD11L: C47.S1 (OUT), D27.P1
unnamed: D20.B1 (OUT), D21.A1 (A)
unnamed: D20.E1 (OUT), D21.B1 (B)
unnamed: D20.H1 (OUT), D21.F1 (A)
unnamed: D20.K1 (OUT), D21.H1 (B)
unnamed: D20.P1 (OUT), D21.N1 (B)
unnamed: D20.M1 (OUT), D21.M1 (A)
unnamed: D20.N2 (OUT), D21.S2 (B)
unnamed: D20.J2 (OUT), D21.L2 (B)
unnamed: D20.U1 (OUT), D21.E2 (B)
unnamed: D20.S1 (OUT), D21.D2 (A)
unnamed: D20.F2 (OUT), D21.K2 (A)
unnamed: D20.L2 (OUT), D21.R2 (A)
unnamed: C52.D2, D31.A1 (IN1), D32.D2
unnamed: C52.E2, D31.D1 (IN), D32.E2
unnamed: C52.F2, D31.F1 (IN), D32.H2
unnamed: C52.N2, D31.L1 (IN), D32.K2
unnamed: C49.E2 (IN2), C49.F1 (OUT)
unnamed: C49.D2 (IN1), C49.K1 (OUT)
unnamed: C46.U2 (IN), C49.F2 (OUT)
unnamed: C47.K2 (IN1), C47.M2 (IN3), C49.C1 (OUT)
unnamed: C50.C1 (OUT), C50.D1 (IN1)
unnamed: C50.B1 (IN2), C50.D2 (IN1), C50.F1 (OUT)
unnamed: C51.E1 (IN), C51.T2
unnamed: C50.H2 (IN1), C51.F1 (OUT)
unnamed: C50.L2 (IN1), C50.M2 (IN2), C50.N1 (OUT)
unnamed: C50.H1 (IN1), C50.N2 (OUT)
unnamed: C50.A1 (IN1), C50.K1 (OUT)
unnamed: C50.E2 (IN2), C50.J1 (IN2), C50.J2 (IN2), D31.K1 (OUT)
unnamed: C50.E1 (IN2), C50.K2 (OUT)
OPAUSEL: C48.D1, C50.F2 (OUT)
PAUSEL: C49.H1 (IN1), C49.J1 (IN2), D31.H1 (OUT), D31.J1 (IN)
POWEROK: B27.V2, C52.M2
SKIPL: C46.P2 (IN1), C48.S1, C52.K2
STROBE: C48.H2, C50.L1 (IN1), C50.M1 (IN2), D31.M1 (OUT)
T2: A04.T2, D04.T2
TP3: C51.H2, D31.B1 (OUT); also elsewhere on the board
TP4: C48.J2, D31.E1 (OUT); also elsewhere on the board
V2: A04.V2, D04.V2
VCC: C46.A2 (VCC), C47.A2 (VCC), C49.A2 (VCC), C50.A2 (VCC), C51.A2 (VCC), C52.A2 (VCC), D20.A2 (VCC), D21.A2 (VCC), D22.A2 (VCC), D31.A2 (VCC); also elsewhere on the board

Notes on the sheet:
Posibus Connectors
MD03L
MD04L
MD05L
MD06L
MD07L
MD08L
INITIALIZE
OTP3
